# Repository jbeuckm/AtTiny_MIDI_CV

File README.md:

# AtTiny85 MIDI-2-CV

Here is a little MIDI interface with a few, inexpensive parts on a single-sided PCB for DIY enthusiasts. 

An ATTINY85 microcontroller ($1.67) implements the SoftwareSerial and MIDI libraries, along with one to control a MCP4822 DAC for pitch and velocity CV outputs. A simple transistor switch enables a full-swing gate output. Pitch Bend messages smoothly change the pitch independent of the gate signal.

### Pitch + CV Normals

The gate jack is normalled to the gate bus of the Eurorack connector. The pitch jack is normalled to the CV bus of the Eurorack connector.

### Set MIDI Channel

A six-byte System Exclusive message can be used to change the channel of the interface.

`F0` sysex start

`77 00 00` manufacturer + model + device

`03` channel (0 for omni) 

`F7` end of message

### Tuning

A trim pot is used to tune the pitch output for 1V/octave. At powerup, before any MIDI mesages are received, the pitch CV should be set to 8.0V.

### Assembly Notes

The MCP4822 library has been modified to sendSPIClock() using `delayMicroseconds()` instead of `delay()` so that pitch bend is smooth.

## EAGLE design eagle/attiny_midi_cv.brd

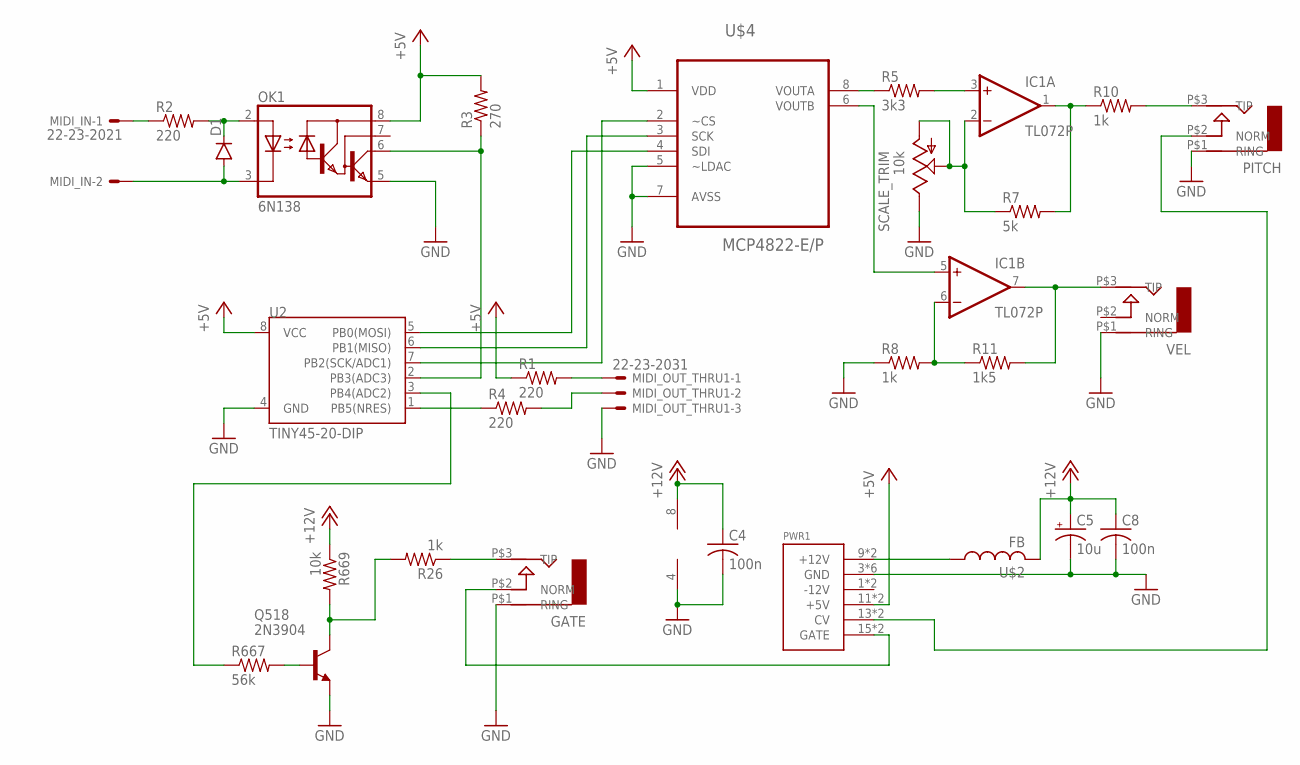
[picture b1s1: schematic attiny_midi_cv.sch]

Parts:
C4, C8: 100n; C050-024X044
C5: 10u; B45181A
D1: DIODE1N4148; DIODE-1N4148
GATE: AUDIO-JACK; ERTHENVAR-JACK-90DEG
IC1: TL072P; DIL08
MIDI_IN: 22-23-2021
MIDI_OUT_THRU1: 22-23-2031
OK1: 6N138; DIL08
PITCH: AUDIO-JACK; ERTHENVAR-JACK-90DEG
PWR1: POWER; POWER_16
Q518: 2N3904; TO92
R1, R2, R4: 220; 0207/7
R3: 270; 0207/7
R5: 3k3; 0207/7
R7: 5k; 0207/7
R8, R10: 1k; 0207/7
R11: 1k5; 0207/7
R26: 1k; 0309/10
R667: 56k; 0207/7
R669: 10k; 0207/7
SCALE_TRIM: 10k; B64W
U2: TINY45-20-DIP; DIP08
U$2: FB
U$4: MCP4822-E/P; DIP254P762X432-8
VEL: AUDIO-JACK; ERTHENVAR-JACK-90DEG

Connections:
+5V: OK1.8 (VCC), PWR1.11 (+5V), PWR1.12 (+5V), R1.1, R3.2, U2.8 (VCC), U$4.1 (VDD)
+12V: C4.1, C5.+, C8.1, IC1.8 (V+), R669.1, U$2.P$2 (2)
GND: C4.2, C5.-, C8.2, GATE.P$1 (RING), IC1.4 (V-), MIDI_OUT_THRU1.3, OK1.5 (GND), PITCH.P$1 (RING), PWR1.3 (GND), PWR1.4 (GND), PWR1.5 (GND), PWR1.6 (GND), PWR1.7 (GND), PWR1.8 (GND), Q518.3 (E), R8.1, SCALE_TRIM.E, U2.4 (GND), U$4.5 (~LDAC), U$4.7 (AVSS), VEL.P$1 (RING)
unnamed: R5.1, U$4.8 (VOUTA)
unnamed: D1.A, MIDI_IN.2, OK1.3 (C)
unnamed: GATE.P$3 (TIP), R26.1
unnamed: PITCH.P$3 (TIP), R10.2
unnamed: IC1.3 (+IN), R5.2
unnamed: D1.C, OK1.2 (A), R2.2
unnamed: MIDI_IN.1, R2.1
unnamed: MIDI_OUT_THRU1.1, R1.2
unnamed: MIDI_OUT_THRU1.2, R4.2
unnamed: PWR1.9 (+12V), PWR1.10 (+12V), U$2.P$1 (1)
unnamed: IC1.2 (-IN), R7.1, SCALE_TRIM.A, SCALE_TRIM.S
unnamed: IC1.6 (-IN), R8.2, R11.1
unnamed: IC1.5 (+IN), U$4.6 (VOUTB)
unnamed: PITCH.P$2 (NORM), PWR1.13 (CV), PWR1.14 (CV)
unnamed: R4.1, U2.1 (PB5(NRES))
unnamed: IC1.7 (OUT), R11.2, VEL.P$3 (TIP)
unnamed: Q518.1 (C), R26.2, R669.2
unnamed: Q518.2 (B), R667.2
unnamed: R667.1, U2.3 (PB4(ADC2))
unnamed: U2.6 (PB1(MISO)), U$4.3 (SCK)
unnamed: U2.5 (PB0(MOSI)), U$4.4 (SDI)
unnamed: IC1.1 (OUT), R7.2, R10.1
unnamed: OK1.6 (VO), R3.1, U2.2 (PB3(ADC3))
unnamed: GATE.P$2 (NORM), PWR1.15 (GATE), PWR1.16 (GATE)
unnamed: U2.7 (PB2(SCK/ADC1)), U$4.2 (~CS)

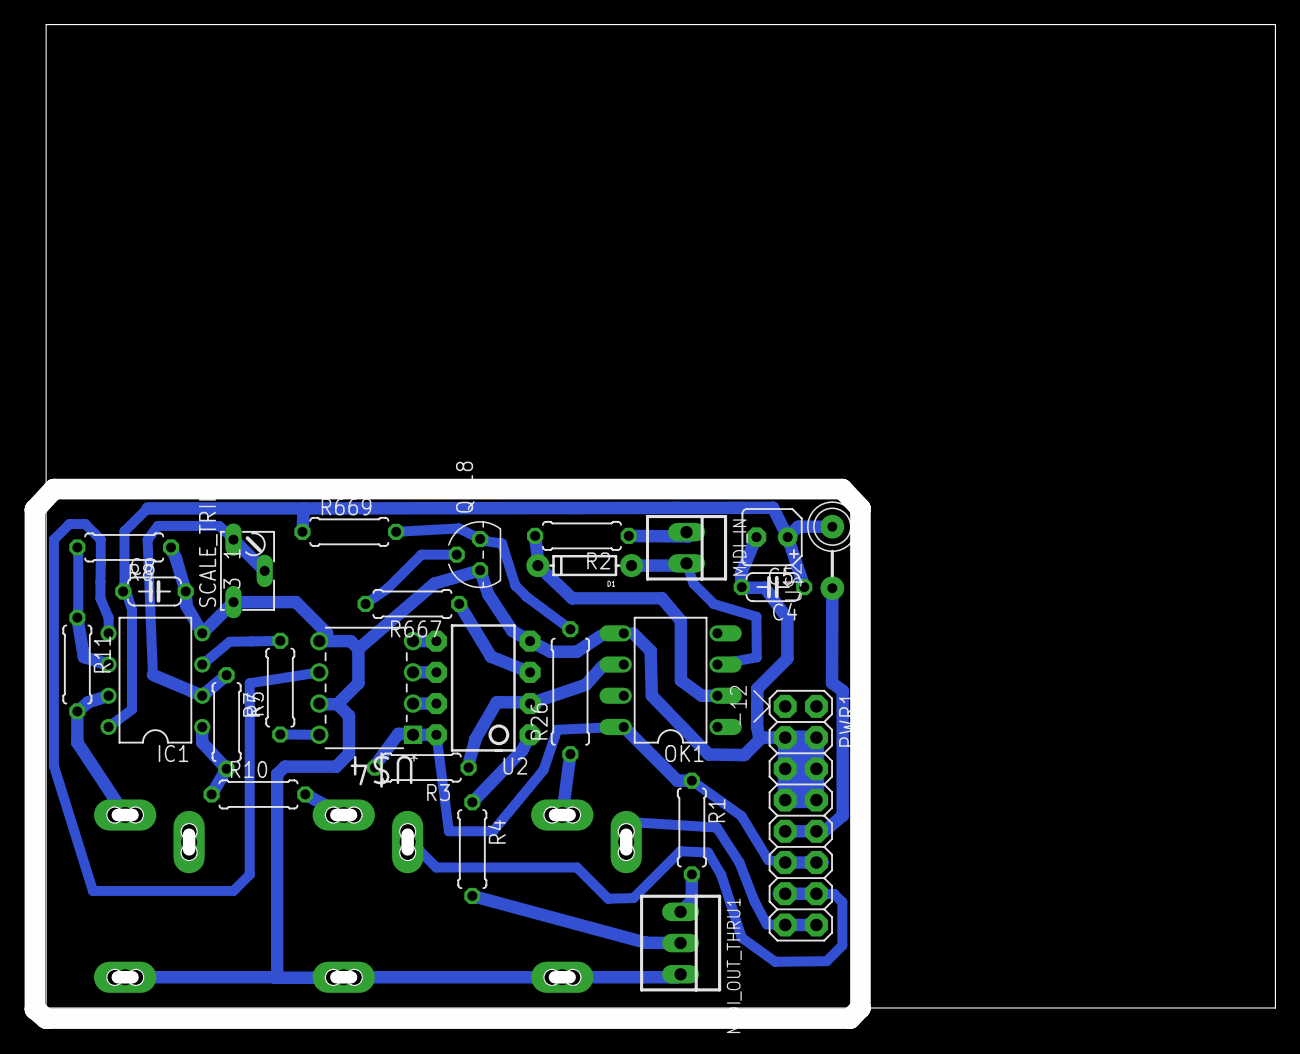
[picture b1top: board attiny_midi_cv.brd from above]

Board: 2 copper layers, 100.1 x 80.0 mm, 29 parts (0 on the bottom side), 28 nets.

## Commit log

2016-06-25 routed
2016-06-25 softwareserialin
2016-06-25 fixed overlap in gnd route
2016-06-25 gcode
2016-06-26 almost tinymidi
2016-06-26 all libraries in and midi instantiated
2016-06-27 tinymidiin begins
2016-06-27 basic note on off working
2016-06-27 filtering notes by channel
2016-06-27 fixed brd and getting channel from eeprom
2016-06-27 widened a trace
2016-06-29 schematic has thru and back to softwareserial
2016-06-30 new gcode and osccal fix for midi in
2016-07-02 sysex sets midi channel
2016-07-02 all notes off and reset controllers
2016-07-04 added a panel

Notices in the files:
parts and their libraries:
SparkFun-DiscreteSemi: Licensing: Creative Commons ShareAlike 4.0 International - https://creativecommons.org/licenses/by-sa/4.0
